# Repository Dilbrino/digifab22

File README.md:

# 🌱 Arduino-basert Vannplantesystem 💧
### Sluttprosjekt i RN DigiFab – Tema: Global oppvarming og klimautfordringer

Dette prosjektet er utviklet som mitt eksamensprosjekt i **Digital Fabrikasjon**.  
Målet var å lage en klimarelevant løsning ved bruk av digital fabrikasjon og elektronikk.  

---

## 📦 Om prosjektet

### 🧠 Kort beskrivelse
Prosjektet er et **Arduino-basert vanningssystem for planter**, som automatisk måler jordfuktighet og vanner planten når det trengs.  
Systemet er designet for å hjelpe folk med å spare vann og ta bedre vare på planter – spesielt i varme og tørre klima.

### 🧩 Valgte teknologier fra DigiFab
- ✅ **3D-printing** – Holder til vanntank og sensorhus
- ✅ **Laserkutting** – Paneler og ramme til systemet
- ✅ **Elektronikk** – Arduino, jordfuktighetssensor, vannpumpe, LED-indikator

---

## 🎯 Hvorfor dette prosjektet?

Global oppvarming fører til:
- Økt tørke og hetebølger
- Mindre tilgjengelig vann
- Planter som sliter med å overleve

💡 Ved å automatisere vanning basert på faktisk fuktighet, kan man redusere vannforbruk og sørge for at planter får akkurat det de trenger.

---

## 🧪 Funksjoner

- 📈 Måler jordfuktighet i sanntid
- 💧 Aktiverer vannpumpe automatisk ved behov
- 🔔 Viser status med LED (grønn/gul/rød)
- 🔌 Drives av Arduino med 5V strømforsyning

---

## 📁 Prosjektstruktur

```bash
📁 code/              # Arduino-kode
📁 design/            # STL-filer og SVG-er for 3D/laser
📁 docs/              # Bilder, rapport og dokumentasjon
📁 fabrication/       # G-code og laserkutt-filer
📄 README.md
📄 video_link.txt     # YouTube-lenke til presentasjonen

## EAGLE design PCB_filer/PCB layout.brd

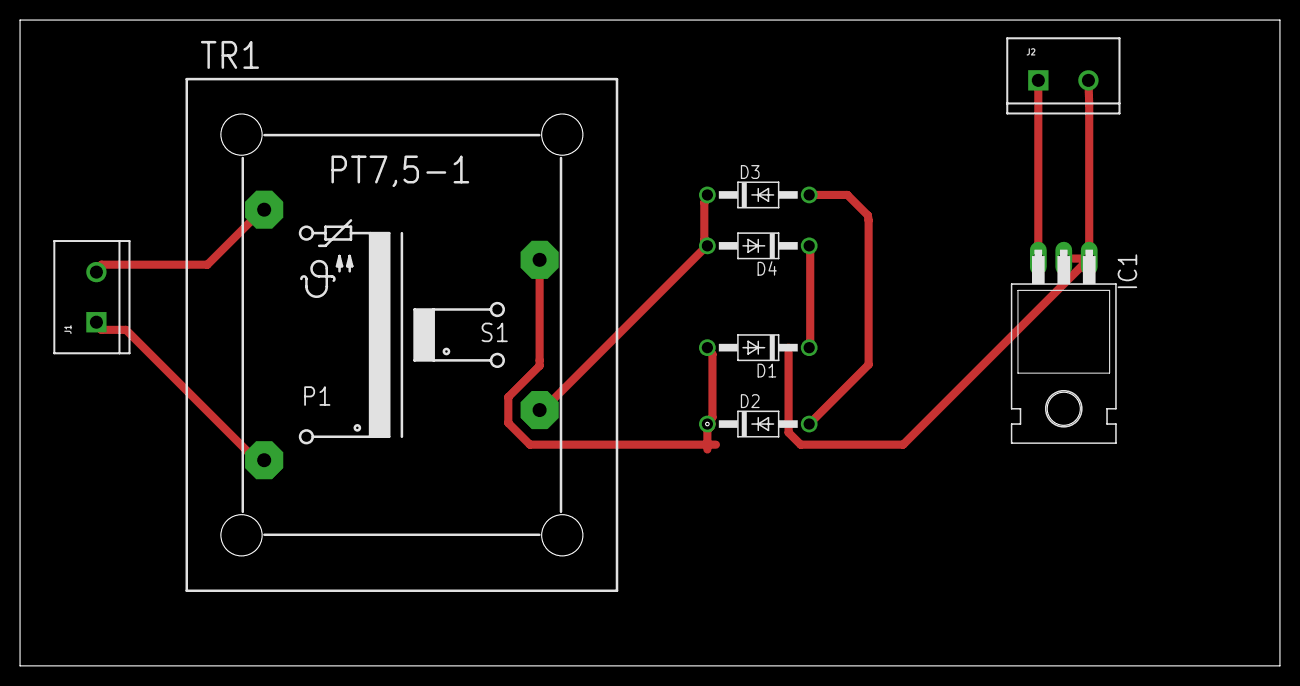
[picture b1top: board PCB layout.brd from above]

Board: 2 copper layers, 125.7 x 64.4 mm, 8 parts (0 on the bottom side), 8 nets.

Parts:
D1, D2, D3, D4: 1N4004; DO41-10
IC1: 7805T; TO220H
J1, J2: SCREWTERMINAL-5MM-2
TR1: PT07,5-1

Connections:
unnamed: D1.A, D2.C
unnamed: D2.A, D3.A
unnamed: D3.C, D4.A, TR1.3
unnamed: IC1.1, IC1.2, J2.2
unnamed: J1.1, TR1.2
unnamed: IC1.3, J2.1
unnamed: J1.2, TR1.1
S$1: D1.C, D4.C

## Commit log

2022-10-02 new uptd
2022-10-02 Delete meg.html
    notworking
2022-10-02 Add files via upload
    new meg fil
2022-11-22 3d.side
    oblig_2
2022-11-22 bilder 3d
    3d_bilder
2022-11-22 up_3d
    3d_up
2022-11-22 new
    br tagg
2022-11-22 grid_row
    grid_up
2022-11-22 css
    grid
2022-11-22 hjem_articel
    article
2022-11-22 hjem_artc
    hjem
2023-01-16 Create 3D_Stl
2023-01-16 3D_stl_file
2023-01-16 repo_link
    Git_repo_link
2023-01-25 Arduino
    Arduino
2023-01-25 Tinkercad
    Tinkercad
2023-01-25 Tinkercad_bilder
    Tinkercad_bilder
2023-01-27 css_update
2023-01-27 Update_style_img
2023-01-27 Schematic kart
2023-01-27 Update_schematic_view
2023-01-27 bilde av arduino oppgave
2023-01-27 bilder Uno_R3
2023-01-27 Update_bilder
2023-01-27 Arduino_bilder_forkalring
2023-02-18 Update_style:css
2023-02-18 Code_bilder_list
2023-02-18 Old_pdf
2023-02-18 new_update
2023-02-18 enda en update
2023-02-18 update_css
2023-02-19 bilder_av_arduino
2023-02-19 lcd_feil
2023-02-19 lys_på_lcd
2023-02-19 fikset_bilde
2023-02-19 style_css
2023-02-19 add_bilder
2023-02-19 logo
2023-02-19 favicon
2023-02-19 favicon_
2023-02-19 ico_new
2023-02-19 icon_up
2023-02-19 new_fav_icon
2023-02-19 add_icon_til_allesider
2023-02-19 text_på_bilder
2023-04-02 ny_page
    ny_digifab
2023-04-02 img_link_update
2023-04-02 style_update
2023-04-02 update_meg.html
2023-04-02 link_Github
2023-04-02 Update_pcb
    link_til_kilder
2023-05-29 Eksamen_fil
2023-05-29 ny_bilder
2023-05-30 ny_bilde
2023-05-30 bilder
2023-05-30 ny bilder
2023-05-30 eksamen_oppgave
2023-05-30 liste
2023-05-30 ny up
2023-05-30 push
2023-05-30 laser_up
2023-05-30 3d_bilde
2023-05-30 legg _video
2023-05-30 artikkel
2023-05-30 test
2023-05-30 film
2023-05-30 resonsiv
2023-05-30 bilde
2023-05-30 kode
2023-05-30 siste
2023-05-30 siste_1_1
2023-05-30 cssss
2023-05-30 mobile enheter css
2023-05-30 style.css
2023-05-30 style_image_radiuos
2023-05-30 html

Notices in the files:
parts and their libraries:
SparkFun-Connectors: Licensing: Creative Commons ShareAlike 4.0 International - https://creativecommons.org/licenses/by-sa/4.0
